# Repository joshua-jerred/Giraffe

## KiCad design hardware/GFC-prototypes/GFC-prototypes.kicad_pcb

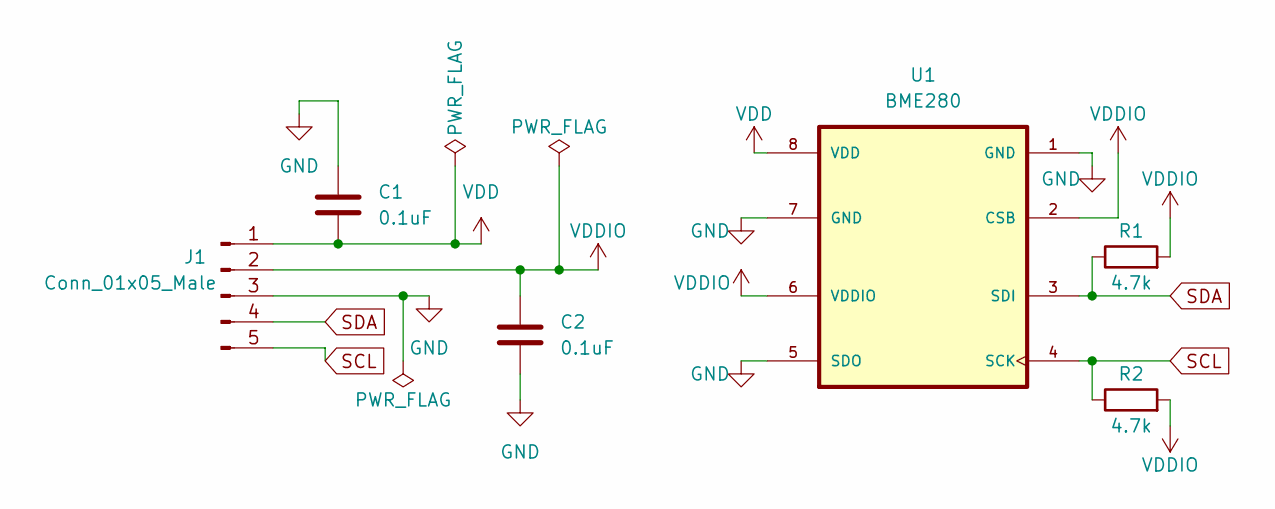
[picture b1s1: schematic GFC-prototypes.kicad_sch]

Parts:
C1, C2: 0.1uF; C_0603_1608Metric_Pad1.08x0.95mm_HandSolder
J1: Conn_01x05_Male; PinHeader_1x05_P2.54mm_Horizontal
R1, R2: 4.7k; R_0603_1608Metric_Pad0.98x0.95mm_HandSolder
U1: BME280; PSON65P250X250X100-8N

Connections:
GND: C1.1, C2.2, J1.3, U1.1 (GND), U1.5 (SDO), U1.7 (GND)
SCL: J1.5, R2.1, U1.4 (SCK)
SDA: J1.4, R1.1, U1.3 (SDI)
VDD: C1.2, J1.1, U1.8 (VDD)
VDDF: C2.1, J1.2, R1.2, R2.2, U1.2 (CSB), U1.6 (VDDIO)

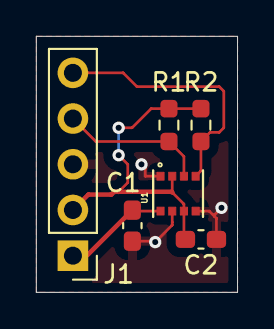
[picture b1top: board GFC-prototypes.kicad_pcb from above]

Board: 2 copper layers, 11.2 x 14.2 mm, 6 parts (0 on the bottom side), 5 nets.

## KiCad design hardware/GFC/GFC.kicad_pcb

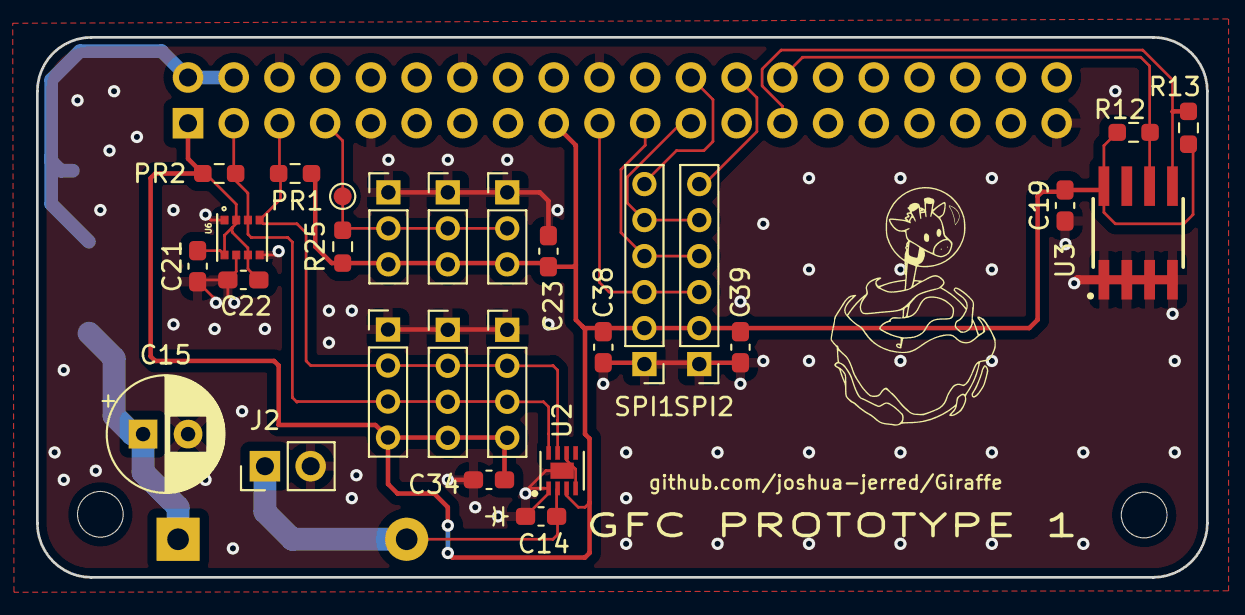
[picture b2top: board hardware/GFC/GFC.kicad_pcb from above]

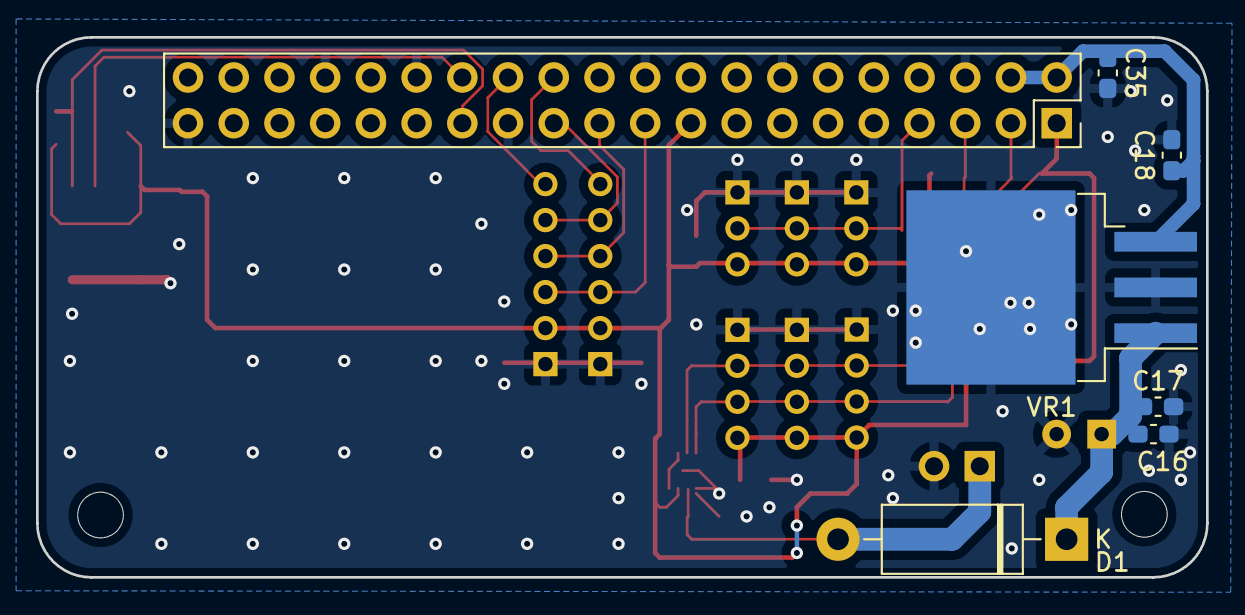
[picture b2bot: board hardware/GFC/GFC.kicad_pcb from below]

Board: 2 copper layers, 65.0 x 30.0 mm, 34 parts (7 on the bottom side), 15 nets.

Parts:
C14, C17, C18, C19, C21, C22, C23, C34, C38, C39: 0.1uF; C_0603_1608Metric_Pad1.08x0.95mm_HandSolder
C15: 100uF; CP_Radial_D6.3mm_P2.50mm
C16: 1uF; C_0603_1608Metric_Pad1.08x0.95mm_HandSolder
C35: 100nF; C_0603_1608Metric_Pad1.08x0.95mm_HandSolder
CPU2: Pi Zero/Zero W; PinSocket_2x20_P2.54mm_Vertical
D1: 1N5400; D_DO-15_P12.70mm_Horizontal
I2C1, I2C2, I2C3: I2C0; PinHeader_1x04_P2.00mm_Vertical
J2: BAT; PinHeader_1x02_P2.54mm_Vertical
PR1, PR2: R; R_0603_1608Metric_Pad0.98x0.95mm_HandSolder
R12, R13: 3.9K; R_0603_1608Metric_Pad0.98x0.95mm_HandSolder
R25: 4.7k; R_0603_1608Metric_Pad0.98x0.95mm_HandSolder
SPI1, SPI2: SPI; PinHeader_1x06_P2.00mm_Vertical
TMP1, TMP2, TMP3: 1-Wire Bus; PinHeader_1x03_P2.00mm_Vertical
TP43: Test Point; TestPoint_Pad_D1.0mm
U2: MAX17048G+T10; SON50P200X200X80-9N
U3: CAT24C32WI-GT3; SOIC127P600X175-8N
U6: BME280; PSON65P250X250X100-8N
VR1: LM7805; TO-263-3_TabPin2

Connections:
1-Wire: CPU2.7, R25.1, TMP1.2, TMP2.2, TMP3.2, TP43.1
+3V3: C19.2, C21.2, C22.1, C23.1, C34.2, C38.2, C39.2, CPU2.1, CPU2.17, I2C1.4, I2C2.4, I2C3.4, PR1.1, PR2.1, R12.2, R13.2, R25.2, SPI1.2, SPI2.2, TMP1.3, TMP2.3, TMP3.3, U2.3 (VDD), U3.8 (VCC), U6.2 (CSB), U6.6 (VDDIO), U6.8 (VDD)
+5V: C18.1, C35.1, CPU2.2, CPU2.4, VR1.3 (VO)
/GFC_HAT/Power/VCC_P: C15.1, C16.1, C17.1, D1.1 (K), VR1.1 (VI)
EEPROM.SCL: CPU2.28, R12.1, U3.6 (SCL)
EEPROM.SDA: CPU2.27, R13.1, U3.5 (SDA)
GND: C14.2, C15.2, C16.2, C17.2, C18.2, C19.1, C21.1, C22.2, C23.2, C34.1, C35.2, C38.1, C39.1, CPU2.6, CPU2.9, CPU2.14, CPU2.20, CPU2.25, CPU2.30, CPU2.34, CPU2.39, I2C1.1, I2C2.1, I2C3.1, J2.2, SPI1.1, SPI2.1, TMP1.1, TMP2.1, TMP3.1, U2.1 (CTG), U2.4 (GND), U2.6 (QSTRT), U2.9 (Exposed_Pad), U3.1 (A0), U3.2 (A1), U3.3 (A2), U3.4 (VSS), U6.1 (GND), U6.5 (SDO), U6.7 (GND), VR1.2 (GND)
I2C0.SCL: CPU2.5, I2C1.2, I2C2.2, I2C3.2, PR1.2, U2.7 (SCL), U6.4 (SCK)
I2C0.SDA: CPU2.3, I2C1.3, I2C2.3, I2C3.3, PR2.2, U2.8 (SDA), U6.3 (SDI)
SPI0.CE0: CPU2.24, SPI1.6
SPI0.CE1: CPU2.26, SPI2.6
SPI0.MISO: CPU2.21, SPI1.4, SPI2.4
SPI0.MOSI: CPU2.19, SPI1.3, SPI2.3
SPI0.SCLK: CPU2.23, SPI1.5, SPI2.5
VCC: C14.1, D1.2 (A), J2.1, U2.2 (CELL)

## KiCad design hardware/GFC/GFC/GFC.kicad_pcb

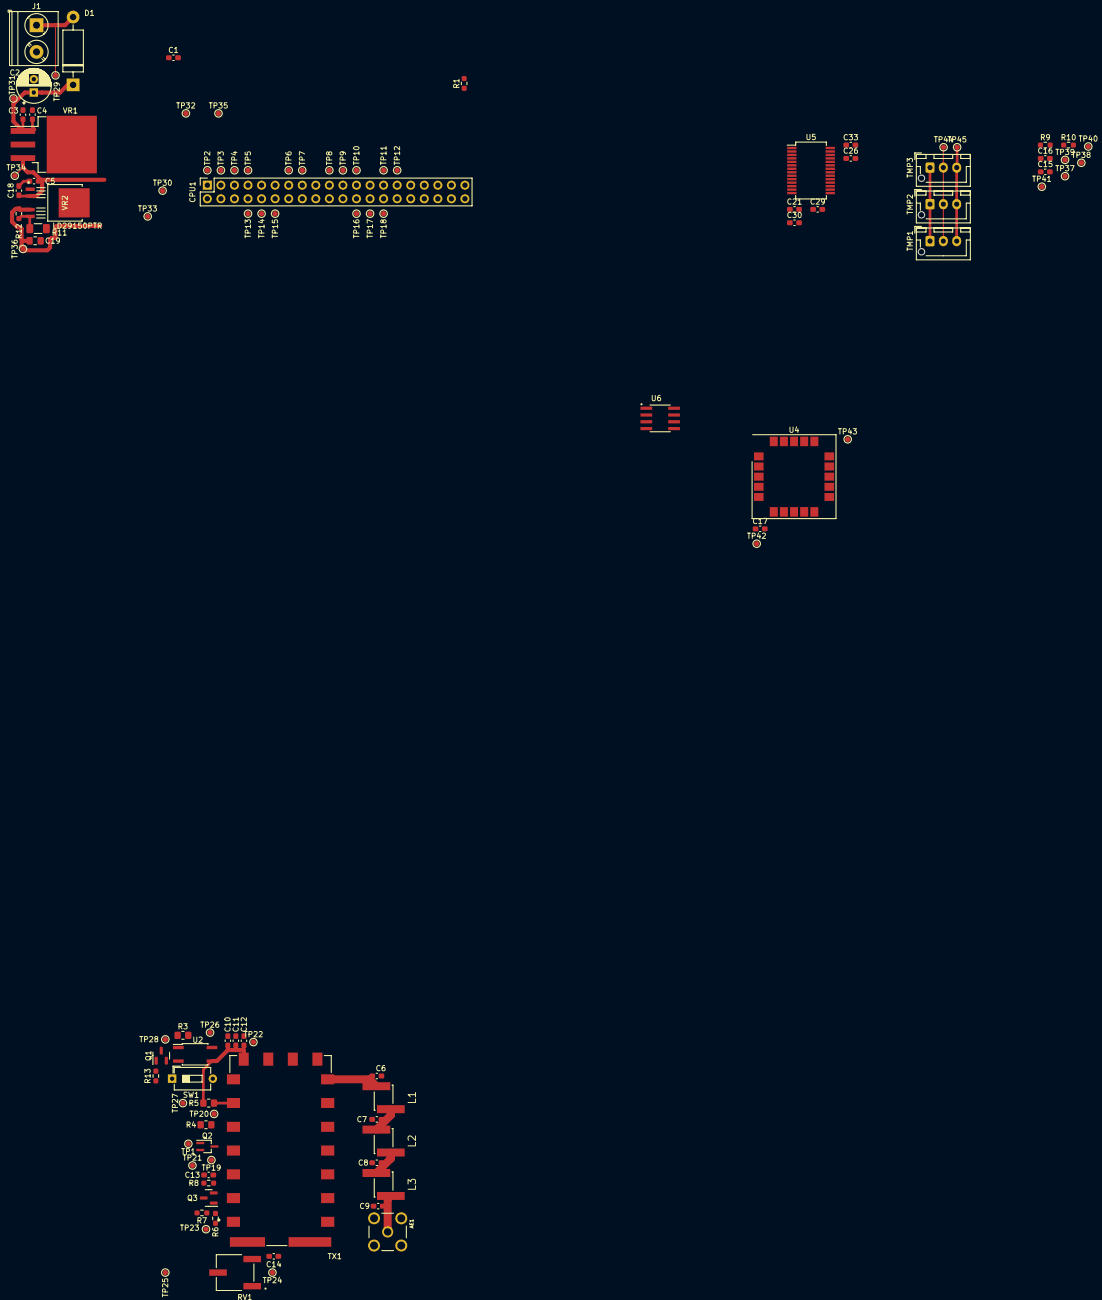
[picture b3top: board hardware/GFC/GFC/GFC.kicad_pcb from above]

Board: 2 copper layers, 103 parts (0 on the bottom side), 48 nets.

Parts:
AE1: Antenna; LINX_CONSMA001-G
C1, C4, C5, C10, C13, C15, C16, C17: 0.1uF; C_0603_1608Metric_Pad1.08x0.95mm_HandSolder
C2: 100uF; CP_Radial_D6.3mm_P2.50mm
C3, C14, C21, C26, C29, C30, C33: 1uF; C_0603_1608Metric_Pad1.08x0.95mm_HandSolder
C6, C9: 20pF; C_0603_1608Metric_Pad1.08x0.95mm_HandSolder
C7, C8: 36pF; C_0603_1608Metric_Pad1.08x0.95mm_HandSolder
C11: 10kpF; C_0603_1608Metric_Pad1.08x0.95mm_HandSolder
C12: 1kpF; C_0603_1608Metric_Pad1.08x0.95mm_HandSolder
C18: 0.33uF; C_0603_1608Metric_Pad1.08x0.95mm_HandSolder
C19: 10uF; C_0805_2012Metric_Pad1.18x1.45mm_HandSolder
CPU1: Pi Zero/Zero W; PinSocket_2x20_P2.54mm_Vertical
D1: 1N5400; D_DO-15_P12.70mm_Horizontal
J1: BAT; TerminalBlock_Phoenix_PT-1,5-2-5.0-H_1x02_P5.00mm_Horizontal
L1, L3: 56nH; IND_AIAC-1812-33NK-T
L2: 68nH; IND_AIAC-1812-33NK-T
Q1, Q3: Q_NPN_BCE; SOT-23
Q2: DMN67D8LW-13; SOT-323_SC-70_Handsoldering
R1, R9, R10: 4.7k; R_0603_1608Metric_Pad0.98x0.95mm_HandSolder
R3: 100; R_0805_2012Metric_Pad1.20x1.40mm_HandSolder
R4: 10k; R_0805_2012Metric_Pad1.20x1.40mm_HandSolder
R5: 10K; R_0805_2012Metric_Pad1.20x1.40mm_HandSolder
R6: 100K; R_0603_1608Metric_Pad0.98x0.95mm_HandSolder
R7: 56K; R_0603_1608Metric_Pad0.98x0.95mm_HandSolder
R8: 1K; R_0603_1608Metric_Pad0.98x0.95mm_HandSolder
R11: 40k; R_1206_3216Metric_Pad1.30x1.75mm_HandSolder
R12: 100k; R_0603_1608Metric_Pad0.98x0.95mm_HandSolder
R13: ?; R_0603_1608Metric_Pad0.98x0.95mm_HandSolder
RV1: 100k; TRIM_3361P-1-104GLF
SW1: H/L_DIP_SW; SW_DIP_SPSTx01_Slide_6.7x4.1mm_W7.62mm_P2.54mm_LowProfile
TMP1, TMP2, TMP3: DS18B20 - Connector; JST_XH_B3B-XH-AM_1x03_P2.50mm_Vertical
TP1, TP2, TP3, TP4, TP5, TP6, TP7, TP8, TP9, TP10, TP11, TP12, TP13, TP14, TP15, TP16, TP17, TP18, TP19, TP20, TP21, TP22, TP23, TP24, TP25, TP26, TP27, TP28, TP29, TP30, TP31, TP32, TP33, TP34, TP35, TP36, TP37, TP38, TP39, TP40, TP41, TP42, TP43, TP44, TP45: Test Point; TestPoint_Pad_D1.0mm
TX1: DRA818V; DORJI_DRA818V
U2: LTV-356T; SO-4_4.4x3.6mm_P2.54mm
U4: SAM-M8Q; ublox_SAM-M8Q
U5: PCM2902C; SSOP-28_5.3x10.2mm_P0.65mm
U6: CAT24C32WI-GT3; SOIC127P600X175-8N
VR1: LM7805; TO-263-3_TabPin2
VR2: LD29150PTR

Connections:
1-Wire: CPU1.7, R1.1, TMP1.2, TMP2.2, TMP3.2, TP5.1, TP44.1
+3V3: C15.1, C16.1, C17.2, CPU1.1, CPU1.17, R1.2, R3.2, R8.1, R9.1, R10.2, TMP1.3, TMP2.3, TMP3.3, TP2.1, TP30.1, TP40.1, TP41.1, TP45.1, U4.2 (VCC_IO), U4.3 (V_BCKP), U4.17 (VCC), U6.8 (VCC)
+4V3: C19.1, R12.1, TP26.1, TP36.1, U2.4, VR2.4 (OUTPUT)
+5V: C5.1, C18.1, CPU1.2, CPU1.4, TP34.1, VR1.3 (VO), VR2.2 (INPUT)
/BMP390 (I2C)/I2C0.SCL: R10.1, TP39.1
/BMP390 (I2C)/I2C0.SDA: R9.2, TP38.1
/DAC/AUDIO.SC_OUT_R: RV1.2, TP25.1
/DRA818/4V3 Controlled: C10.2, C11.2, C12.2, R5.2, TP22.1, TP27.1, TX1.8 (VBAT), U2.3
/DRA818/DRA SQ: R6.1, TP23.1, TX1.1 (SQ)
/Power/VCC_P: C2.1, C3.1, C4.1, D1.1 (K), TP31.1, VR1.1 (VI)
DAC.LRC: CPU1.12, CPU1.35, TP15.1
EEPROM.SCL: CPU1.28, TP18.1, U6.6 (SCL)
EEPROM.SDA: CPU1.27, TP11.1, U6.5 (SDA)
GND: C1.2, C2.2, C3.2, C4.2, C5.2, C6.2, C7.2, C8.2, C9.2, C10.1, C11.1, C12.1, C15.2, C16.2, C17.1, C18.2, C19.2, C21.2, C26.2, C29.2, C30.2, C33.2, CPU1.6, CPU1.9, CPU1.14, CPU1.20, CPU1.25, CPU1.30, CPU1.34, CPU1.39, J1.2, Q1.3 (E), Q2.2 (S), Q3.3 (E), R7.2, R11.2, RV1.1, SW1.1, TMP1.1, TMP2.1, TMP3.1, TP37.1, TX1.9 (GND), TX1.10 (GND), U4.1 (GND), U4.4 (GND), U4.5 (GND), U4.6 (GND), U4.10 (GND), U4.11 (GND), U4.15 (GND), U4.16 (GND), U4.20 (GND), U5.4 (DGNDU), U5.11 (AGNDC), U5.18 (AGNDP), U5.22 (AGNDX), U5.26 (DGND), U6.1 (A0), U6.2 (A1), U6.3 (A2), U6.4 (VSS), VR1.2 (GND), VR2.3 (GND)
GPIO.DRA_PTT: CPU1.29, R4.1, TP12.1
GPIO.DRA_PWR_CONTROL: CPU1.13, R13.2, TP6.1
GPIO.DRA_SQ: CPU1.15, Q3.2 (C), R8.2, TP7.1
I2C0.SCL: CPU1.5, TP4.1, TP33.1, TP43.1, U4.12 (SCL)
I2C0.SDA: CPU1.3, TP3.1, TP32.1, TP42.1, U4.9 (SDA)
unnamed: AE1.1 (A), C9.1, L3.2
unnamed: C6.1, L1.1, TX1.12 (ANT)
unnamed: C7.1, L1.2, L2.1
unnamed: C8.1, L2.2, L3.1
unnamed: C13.1, TP21.1, TX1.3 (AF_OUT)
unnamed: C21.1, U5.3 (VBUS)
unnamed: C26.1, U5.17 (VCCP1I)
unnamed: C29.1, U5.8 (SEL0), U5.9 (SEL1), U5.27 (VDDI)
unnamed: C30.1, U5.23 (VCCXI)
unnamed: C33.1, U5.19 (VCCP2I)
unnamed: Q1.1 (B), R13.1
unnamed: Q1.2 (C), TP28.1, U2.2
unnamed: Q2.1 (G), R4.2, TP1.1
unnamed: Q2.3 (D), TP19.1, TX1.5 (PTT)
unnamed: Q3.1 (B), R6.2, R7.1
unnamed: R3.1, U2.1
unnamed: R5.1, TP20.1, TX1.6 (PD)
unnamed: R11.1, R12.2, TP35.1, VR2.5 (ADJ/N-C-*)
unnamed: C14.1, RV1.3, TP24.1
unnamed: SW1.2, TX1.7 (H/L)
unnamed: C14.2, TX1.18 (MIC_IN)
SPI0.CE0: CPU1.24, TP16.1
SPI0.CE1: CPU1.26, TP17.1
SPI0.MISO: CPU1.21, TP9.1
SPI0.MOSI: CPU1.19, TP8.1
SPI0.SCLK: CPU1.23, TP10.1
UART0.PI_RXD: CPU1.10, TP14.1, TX1.17 (TXD)
UART0.PI_TXD: CPU1.8, TP13.1, TX1.16 (RXD)
VCC: C1.1, D1.2 (A), J1.1, TP29.1

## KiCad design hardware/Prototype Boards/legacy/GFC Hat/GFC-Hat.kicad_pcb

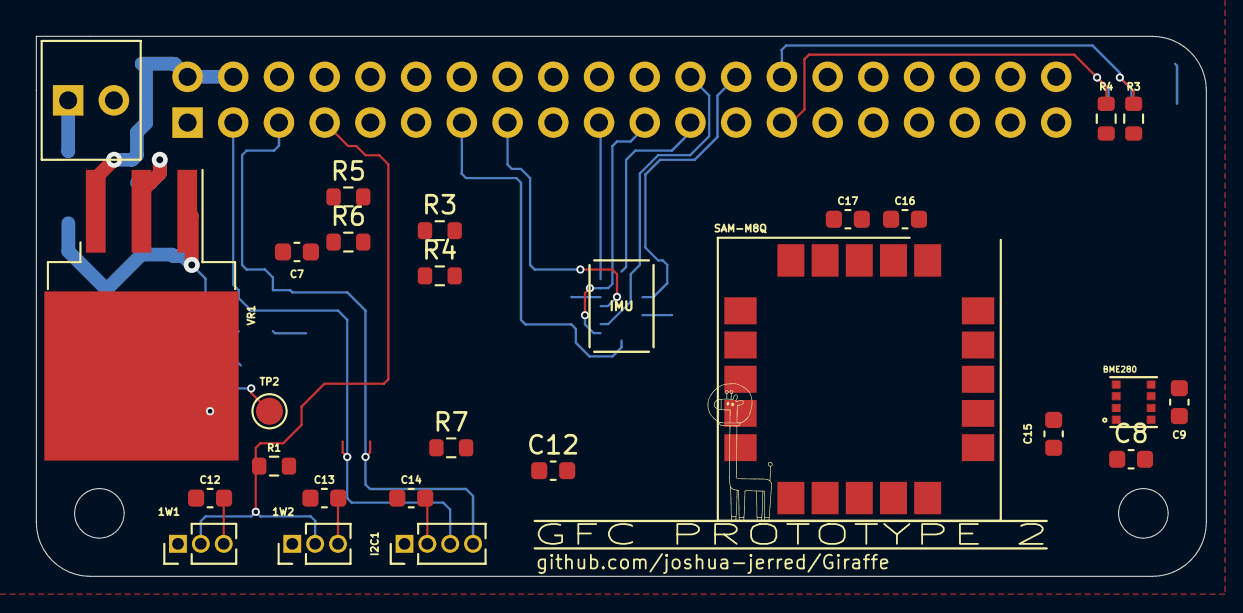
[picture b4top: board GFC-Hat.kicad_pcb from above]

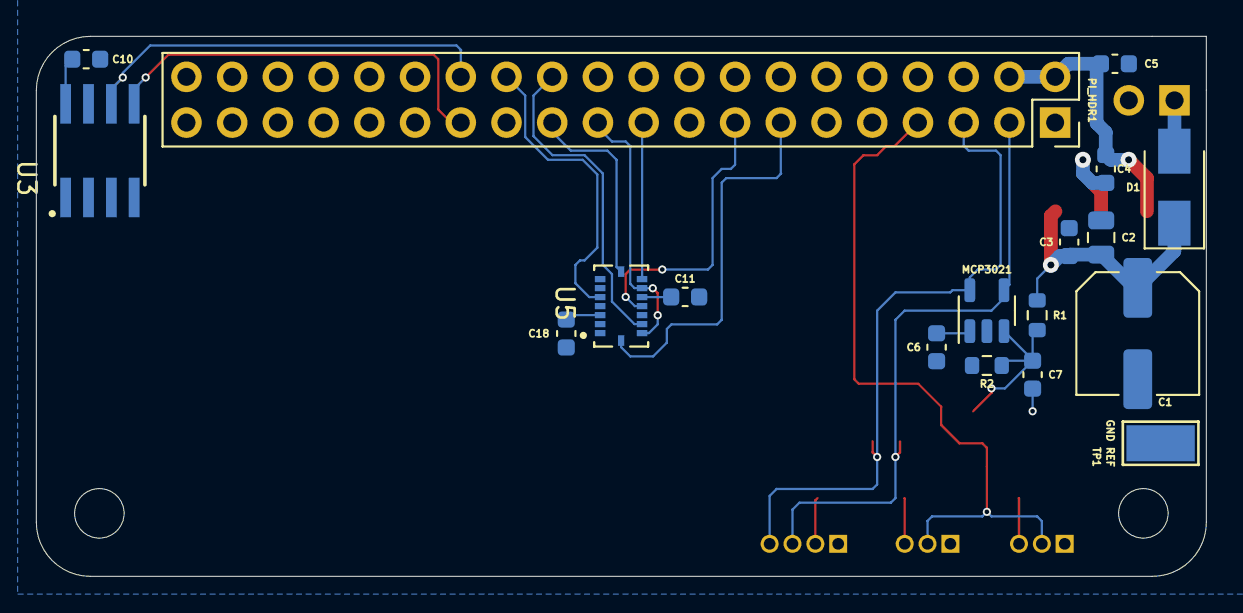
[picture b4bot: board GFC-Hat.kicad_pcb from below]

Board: 4 copper layers, 65.0 x 30.0 mm, 44 parts (18 on the bottom side), 19 nets.

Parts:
1W1, 1W2: 1-Wire; PinHeader_1x03_P1.27mm_Vertical
C1: 100µF; C_Elec_6.3x7.7
C2: 1µF; C_0805_2012Metric
C3, C4, C5, C6, C7, C7#2, C8, C9, C10, C11, C12, C12#2, C13, C14, C15, C16, C17, C18: 0.1µF; C_0603_1608Metric
D1: 2A LFV; D_SMA
I2C1: I²C; PinHeader_1x04_P1.27mm_Vertical
J1: BAT; OSTVN02A150 2x1 Terminal Block
PI_HDR1: PI; PinSocket_2x20_P2.54mm_Vertical
R1, R1#2: 30kΩ; R_0603_1608Metric
R2: 7.5kΩ; R_0603_1608Metric
R3, R3#2, R4, R4#2: 3.9kΩ; R_0603_1608Metric
R5, R6: *; R_0603_1608Metric
R7: 4.7kΩ; R_0603_1608Metric
TP1: GND REF; TestPoint_Keystone_5019_Minature
TP2: BAT REF; TestPoint_Pad_D1.5mm
U1: MCP3021; SOT-23-5
U2: BME280; PSON65P250X250X100-8N
U3: CAT24C32; SOIC127P600X175-8N
U4: SAM-M8Q; ublox_SAM-M8Q
U5: BMI088; PQFN50P450X300X100-16N
VR1: LM7805; TO-263-3_TabPin2

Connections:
1-Wire: 1W1.2, 1W2.2, PI_HDR1.7 (GCLK0/GPIO4), R7.2
+3V3: 1W1.3, 1W2.3, C6.2, C8.2, C9.2, C10.2, C11.2, C12.2, C12#2.2, C13.2, C14.1, C15.2, C16.2, C17.1, C18.2, I2C1.2, PI_HDR1.1 (3V3), PI_HDR1.17 (3V3), R3.1, R3#2.1, R4.1, R4#2.1, R5.1, R6.2, R7.1, U1.1 (VDD), U2.2 (CSB), U2.6 (VDDIO), U2.8 (VDD), U3.8 (VCC), U4.2 (VCC_IO), U4.3 (V_BCKP), U4.17 (VCC), U5.3 (VDD), U5.11 (VDDIO)
+5V: C4.1, C5.2, PI_HDR1.2 (5V), PI_HDR1.4 (5V), VR1.3 (VO)
+BATT: D1.2 (A), J1.1
/BAT Reference Voltage: C7.2, C7#2.2, R1.2, R1#2.2, R2.1, TP2.1, U1.3 (A_IN)
BAT Polarized: C1.1, C2.1, C3.1, D1.1 (K), R1.1, R1#2.1, VR1.1 (VI)
BMI088 Int1: PI_HDR1.33 (PWM1/GPIO13), U5.16 (INT1)
BMI088 Int3: PI_HDR1.15 (GPIO22), U5.12 (INT3)
EEPROM.SCL: PI_HDR1.28 (ID_SC/GPIO1), R4.2, R4#2.2, U3.6 (SCL)
EEPROM.SDA: PI_HDR1.27 (ID_SD/GPIO0), R3.2, R3#2.2, U3.5 (SDA)
GND: 1W1.1, 1W2.1, C1.2, C2.2, C3.2, C4.2, C5.1, C6.1, C7.1, C7#2.1, C8.1, C9.1, C10.1, C11.1, C12.1, C12#2.1, C13.1, C14.2, C15.1, C16.1, C17.2, C18.1, I2C1.1, J1.2, PI_HDR1.6 (GND), PI_HDR1.9 (GND), PI_HDR1.14 (GND), PI_HDR1.20 (GND), PI_HDR1.25 (GND), PI_HDR1.30 (GND), PI_HDR1.34 (GND), PI_HDR1.39 (GND), R2.2, TP1.1, U1.2 (GND), U2.1 (GND), U2.5 (SDO), U2.7 (GND), U3.1 (A0), U3.2 (A1), U3.3 (A2), U3.4 (VSS), U4.1 (GND), U4.4 (GND), U4.5 (GND), U4.6 (GND), U4.10 (GND), U4.11 (GND), U4.15 (GND), U4.16 (GND), U4.20 (GND), U5.2 (NC), U5.4 (GNDA), U5.6 (GNDIO), U5.7 (PS), VR1.2 (GND)
GPS TX-Ready: PI_HDR1.37 (GPIO26), U4.13 (TXD)
I2C0.SCL: I2C1.3, PI_HDR1.5 (SCL/GPIO3), R6.1, U1.5 (SCL), U2.4 (SCK), U4.12 (SCL)
I2C0.SDA: I2C1.4, PI_HDR1.3 (SDA/GPIO2), R5.2, U1.4 (SDA), U2.3 (SDI), U4.9 (SDA)
SPI0.CE0: PI_HDR1.24 (~CE0/GPIO8), U5.14 (CSB1)
SPI0.CE1: PI_HDR1.26 (~CE1/GPIO7), U5.5 (CSB2)
SPI0.MISO: PI_HDR1.21 (MISO0/GPIO9), U5.10 (SDO2), U5.15 (SDO1)
SPI0.MOSI: PI_HDR1.19 (MOSI0/GPIO10), U5.9 (SDA/SDI)
SPI0.SCLK: PI_HDR1.23 (SCLK0/GPIO11), U5.8 (SCL/SCK)

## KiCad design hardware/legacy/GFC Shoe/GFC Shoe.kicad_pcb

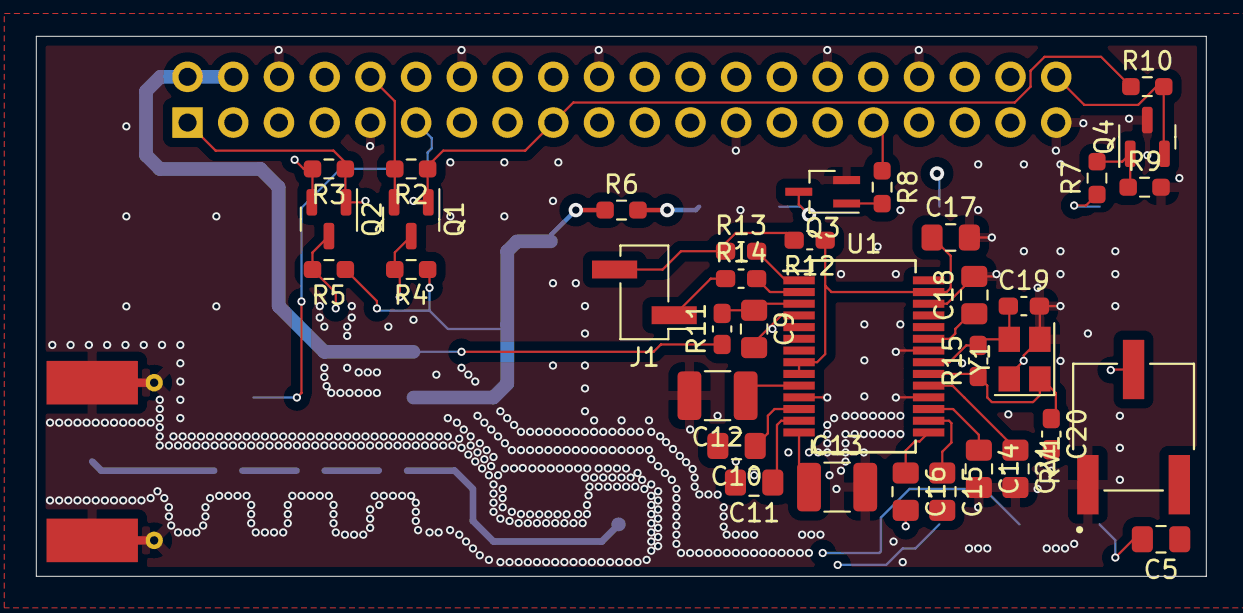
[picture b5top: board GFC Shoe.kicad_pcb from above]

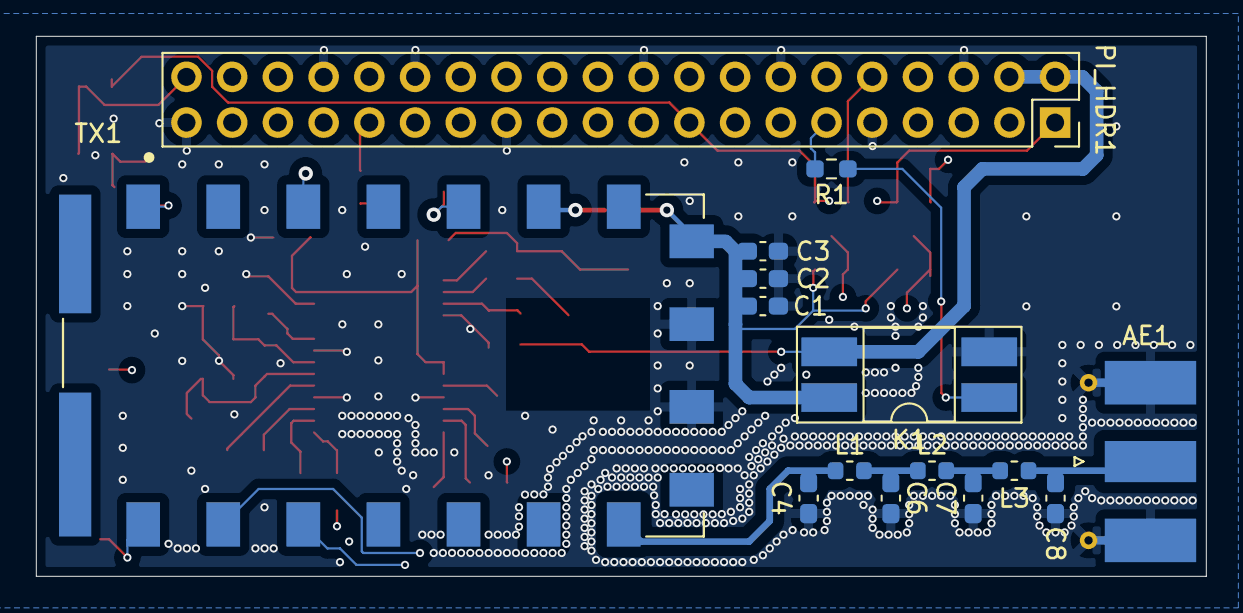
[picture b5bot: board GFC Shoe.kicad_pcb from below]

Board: 4 copper layers, 65.0 x 30.0 mm, 51 parts (15 on the bottom side), 42 nets.

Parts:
AE1: Antenna_Shield; SMA_Molex_73251-1153_EdgeMount_Horizontal
C1: 0.1uF; C_0603_1608Metric_Pad1.08x0.95mm_HandSolder
C2: 10kpF; C_0603_1608Metric_Pad1.08x0.95mm_HandSolder
C3: 1kpF; C_0603_1608Metric_Pad1.08x0.95mm_HandSolder
C4, C8: 20pF; C_0603_1608Metric_Pad1.08x0.95mm_HandSolder
C5, C9, C10, C11, C14, C15, C16, C17, C18, C21: 1uF; C_0805_2012Metric_Pad1.18x1.45mm_HandSolder
C6, C7: 36pF; C_0603_1608Metric_Pad1.08x0.95mm_HandSolder
C12, C13: 10uF; C_1210_3225Metric_Pad1.33x2.70mm_HandSolder
C19, C20: 10pF; C_0603_1608Metric_Pad1.08x0.95mm_HandSolder
J1: USB; PinHeader_1x02_P2.54mm_Vertical_SMD_Pin1Left
K1: TLP241A; DIP-4_W8.89mm_SMDSocket_LongPads
L1, L3: 56nH; L_0603_1608Metric
L2: 68nH; L_0603_1608Metric
PI_HDR1: PI; PinSocket_2x20_P2.54mm_Vertical
Q1, Q2: BSS138; SOT-23
Q3: DMN67D8LW-13; SOT-323_SC-70_Handsoldering
Q4: Q_NPN_BCE; SOT-23
R1: 270; R_0603_1608Metric_Pad0.98x0.95mm_HandSolder
R2, R3, R4, R5, R8: 10k; R_0603_1608Metric_Pad0.98x0.95mm_HandSolder
R6: 10K; R_0603_1608Metric_Pad0.98x0.95mm_HandSolder
R7: 100K; R_0603_1608Metric_Pad0.98x0.95mm_HandSolder
R9: 56K; R_0603_1608Metric_Pad0.98x0.95mm_HandSolder
R10: 1K; R_0603_1608Metric_Pad0.98x0.95mm_HandSolder
R11: 2.2; C_0603_1608Metric_Pad1.08x0.95mm_HandSolder
R12: 1.5k; C_0603_1608Metric_Pad1.08x0.95mm_HandSolder
R13, R14: 22; C_0603_1608Metric_Pad1.08x0.95mm_HandSolder
R15: 1M; C_0603_1608Metric_Pad1.08x0.95mm_HandSolder
RV1: 100k; TRIM_3361P-1-104GLF
TX1: SA868; DORJI_DRA818V
U1: PCM2902C; SSOP-28_5.3x10.2mm_P0.65mm
Y1: Crystal ECS33B; Crystal_SMD_3225-4Pin_3.2x2.5mm

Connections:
5VC: C1.2, C2.2, C3.2, K1.4 (Drain), R4.1, R5.1, R6.1, TX1.8 (VBAT)
+3V3: PI_HDR1.1 (3V3), PI_HDR1.17 (3V3), Q1.1 (G), Q2.1 (G), R2.1, R3.1, R10.1
+5V: K1.3 (Drain), PI_HDR1.2 (5V), PI_HDR1.4 (5V), R11.1
/SA868/A_IN: C16.2, RV1.2
/SA868/A_IN Filtered: C5.2, TX1.18 (MIC_IN)
/SA868/A_OUT: C11.2, TX1.3 (AF_OUT)
/SA868/PD: R6.2, TX1.6 (PD)
/SA868/PTT: Q3.3 (D), TX1.5 (PTT)
/SA868/RF OUT: C4.1, L1.1, TX1.12 (ANT)
/SA868/RF_OUT_FILTERED: AE1.1 (A), C8.1, L3.2
/SA868/RXD 5V: Q2.3 (D), R5.2, TX1.16 (RXD)
/SA868/Radio UART RX: PI_HDR1.8 (GPIO14/TXD), Q2.2 (S), R3.2
/SA868/Radio UART TX: PI_HDR1.10 (GPIO15/RXD), Q1.2 (S), R2.2
/SA868/SQ: R7.1, TX1.1 (SQ)
/SA868/TXD 5V: Q1.3 (D), R4.2, TX1.17 (TXD)
/Sound Card/D+: J1.2, R12.2, R13.1
/Sound Card/D-: J1.1, R14.1
GND: AE1.2 (Shield), C1.1, C2.1, C3.1, C4.2, C6.2, C7.2, C8.2, C9.2, C12.2, C13.2, C14.2, C17.2, C18.2, C19.2, C20.2, C21.2, K1.2 (Cathode), PI_HDR1.6 (GND), PI_HDR1.9 (GND), PI_HDR1.14 (GND), PI_HDR1.20 (GND), PI_HDR1.25 (GND), PI_HDR1.30 (GND), PI_HDR1.34 (GND), PI_HDR1.39 (GND), Q3.2 (S), Q4.3 (E), R9.2, RV1.1, TX1.9 (GND), TX1.10 (GND), U1.4 (DGNDU), U1.11 (AGNDC), U1.18 (AGNDP), U1.22 (AGNDX), U1.26 (DGND), Y1.2, Y1.4
GPIO PTT: PI_HDR1.31 (GCLK2/GPIO6), R8.1
GPIO SQ: PI_HDR1.40 (GPIO21/SCLK1), Q4.2 (C), R10.2
unnamed: C5.1, RV1.3
unnamed: C6.1, L1.2, L2.1
unnamed: C7.1, L2.2, L3.1
unnamed: C9.1, R11.2, U1.3 (VBUS)
unnamed: C10.1, U1.12 (VINL)
unnamed: C11.1, U1.13 (VINR)
unnamed: C12.1, U1.10 (VCCCI)
unnamed: C13.1, U1.14 (VCOM)
unnamed: C14.1, U1.17 (VCCP1I)
unnamed: C15.1, U1.16 (VOUTL)
unnamed: C16.1, U1.15 (VOUTR)
unnamed: C17.1, R12.1, U1.8 (SEL0), U1.9 (SEL1), U1.27 (VDDI)
unnamed: C18.1, U1.23 (VCCXI)
unnamed: C19.1, R15.2, U1.21 (XTI), Y1.3
unnamed: C21.1, U1.19 (VCCP2I)
unnamed: K1.1 (Anode), R1.1
unnamed: Q3.1 (G), R8.2
unnamed: Q4.1 (B), R7.2, R9.1
unnamed: R13.2, U1.1 (D+)
unnamed: R14.2, U1.2 (D-)
unnamed: C20.1, R15.1, U1.20 (XTO), Y1.1
Radio Power Control: PI_HDR1.11 (GPIO17), R1.2

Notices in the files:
parts and their libraries:
Copyright 2021 Accelerated Designs. All rights reserved.
